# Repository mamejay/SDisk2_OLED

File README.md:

***** Updated Version Using SMD Components *****

I have updated the PCB to use all SMD components and tactile switches
I have re-compiled the code and confirmed is working.

# SDisk2 - Simplified

Disk II flopy drive emulator for Apple 2 computers

Objective. an Open Source Disk II floppy Disk emulator that is easy to make.  
See readme in firmware and PCB section for related info.

## Changes

* 27Mhz Xtal.
* OLED only. All LCD and Nokia LCD codes have been removed.
* All Screen rotation code removed.
* Buttons re-arranged

## To-do

1. Better documentaion of the code.

This project will be migrated to an ESP32 based SDISKII.
<https://github.com/terenceang/sdisk2esp>

## Authors

* (c) 2010 Koichi NISHIDA <tulip-house@msf.biglobe.ne.jp>
* (c) 2012 Victor Trucco
* (c) 2012 Fábio Belavenuto
* (c) 2015 Alexandre Suaide
* (c) 2022 Terence Ang

## License

This work is released under the version 3 of the GNU General Public License.

'''NOTE:'''
The current legal status of this code is uncertain.

Fábio and Alexandre have published files with a header that references the version 3 of the GNU General Public License, but it is not clear yet what's the licensing chosen by the original author, Koichi Nishida.

This repository will be updated once the actual licensing info is clarified by the authors.

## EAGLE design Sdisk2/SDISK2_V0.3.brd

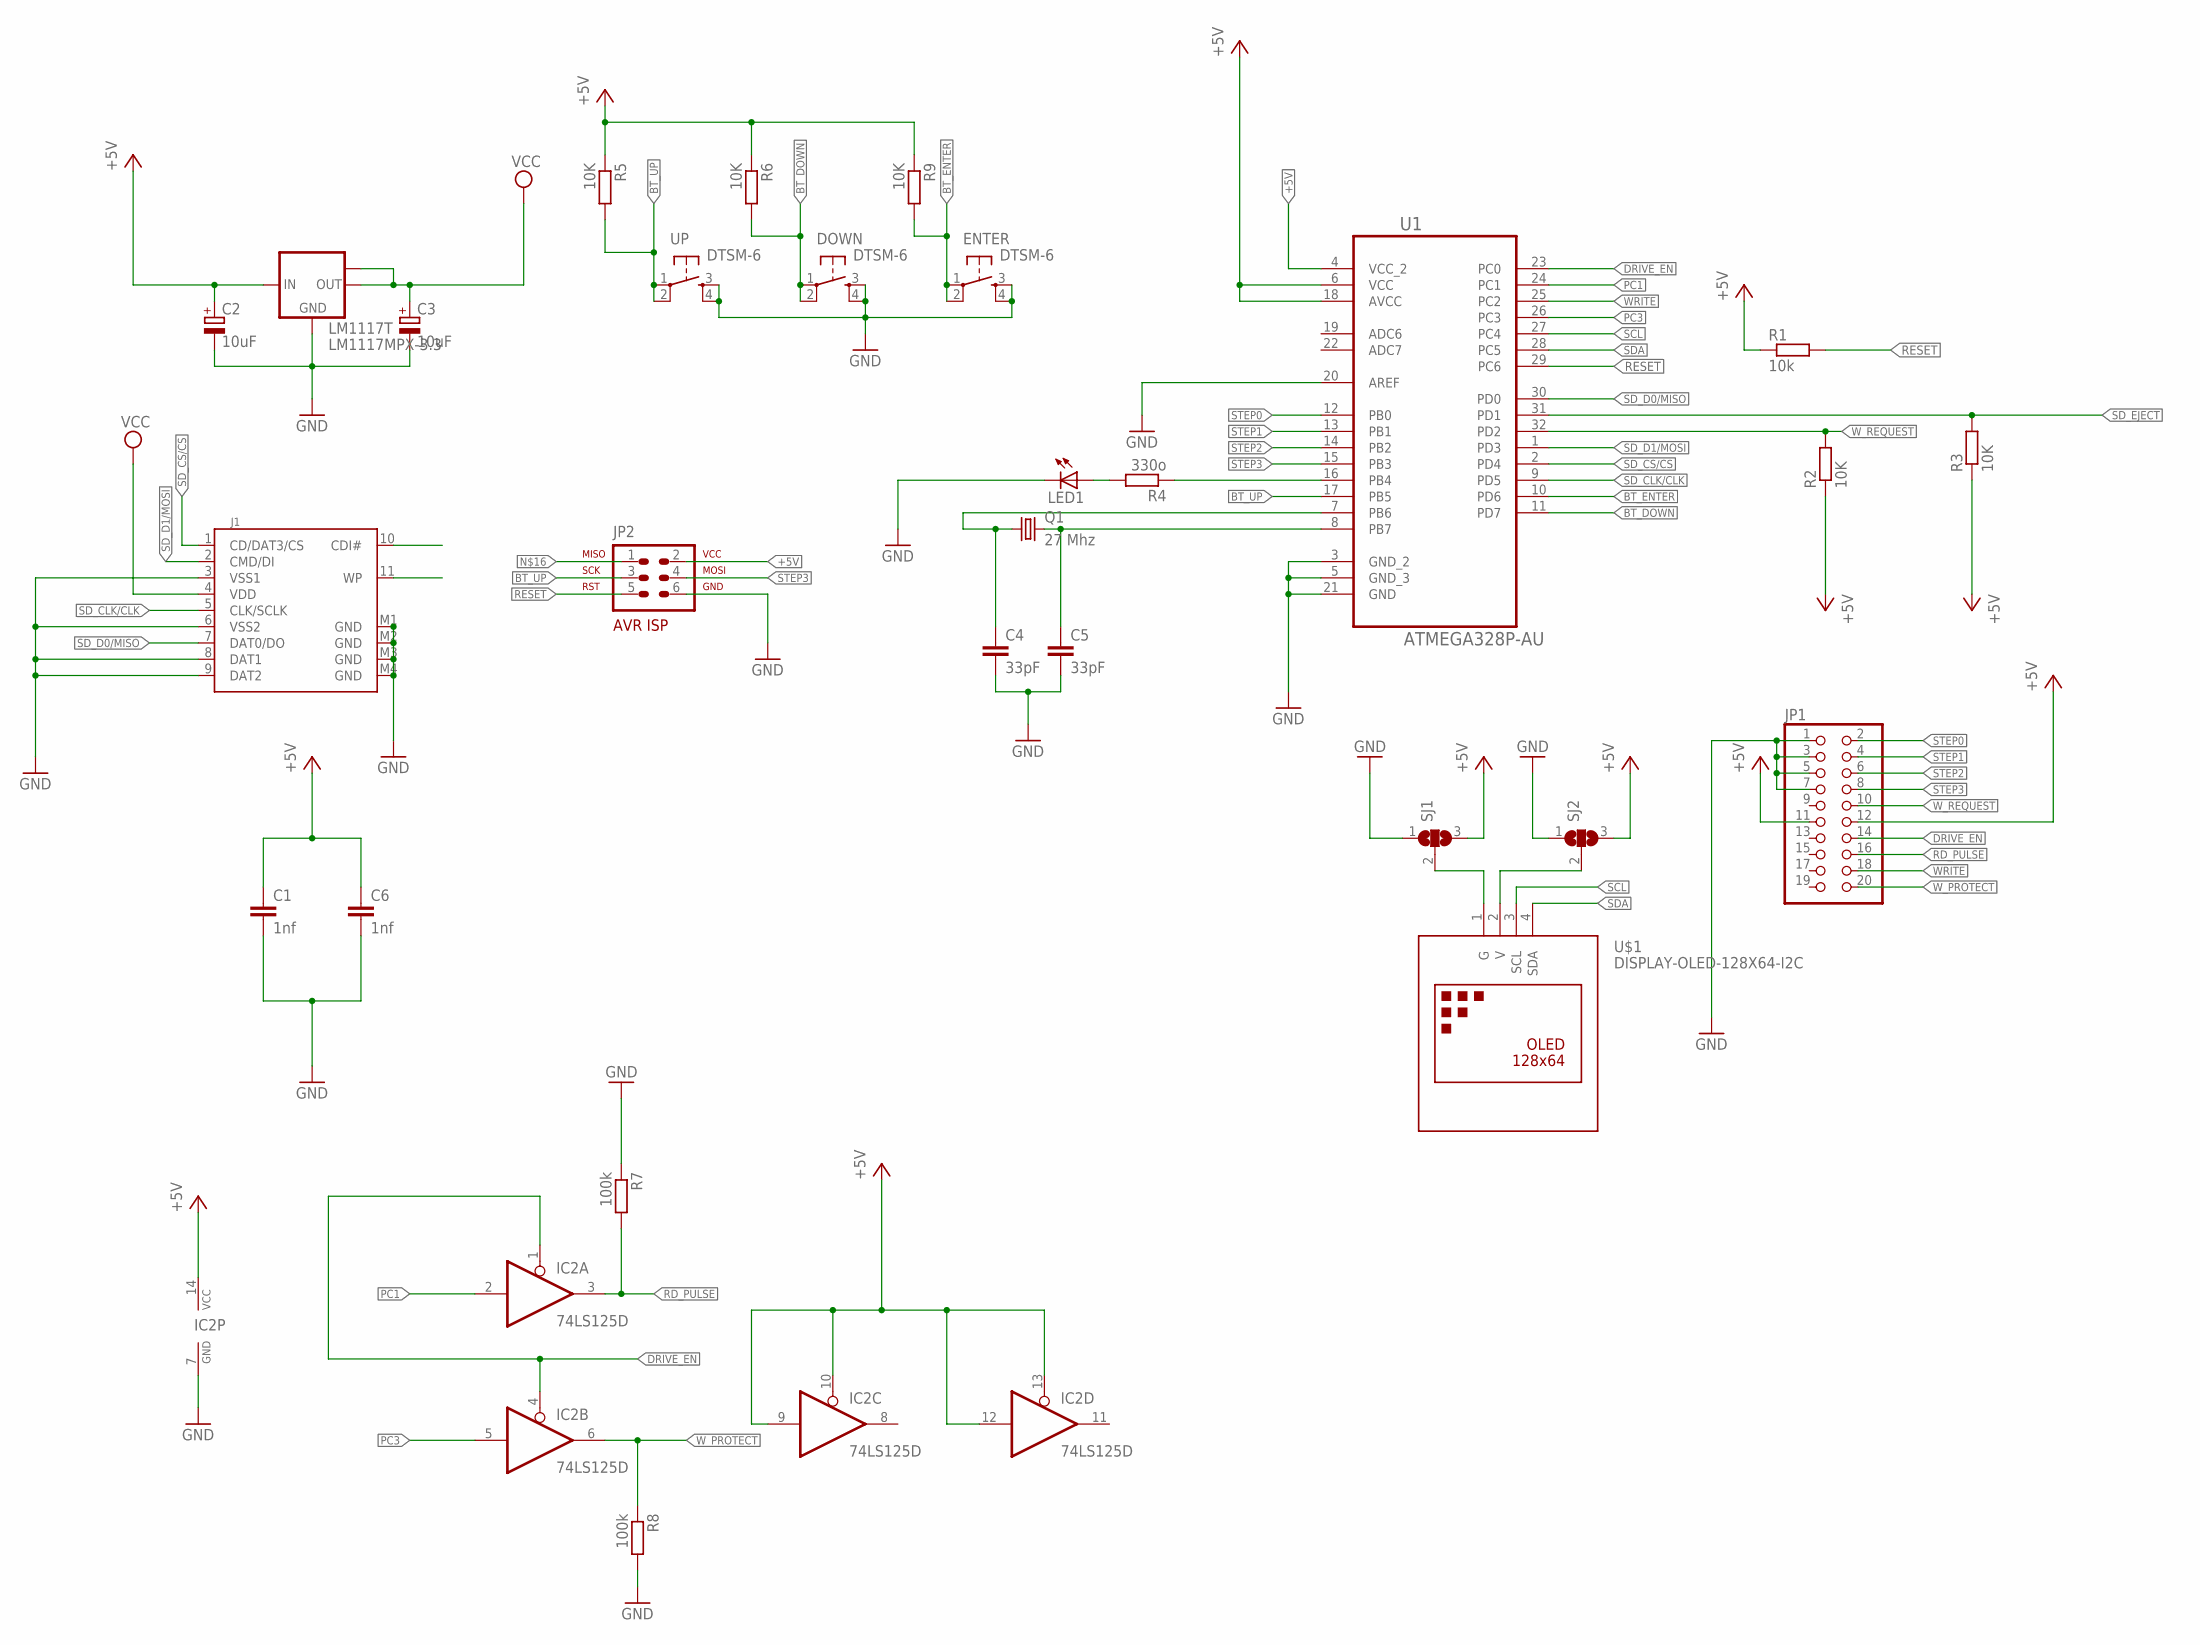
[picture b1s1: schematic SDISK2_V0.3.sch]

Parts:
C1, C6: 1nf; C0805
C2, C3: 10uF; 153CLV-0405
C4, C5: 33pF; C0805
DOWN: DTSM-6
ENTER: DTSM-6
IC2: 74LS125D; SO14
J1: SDCARD; SDCMF-10915W010
JP1: PINHD-2X10_IDC2X10_IDC_NEW; 2X10_IDC
JP2: AVR-ISP-6VERT; AVR-ISP-6
LED1: LEDSML1206; SML1206
LM1117T: LM1117MPX-3.3; SOT223
Q1: 27 Mhz; HC49UP
R1: 10k; R0805
R2, R3, R5, R6, R9: 10K; R0805
R4: 330o; R0805
R7, R8: 100k; R0805
SJ1, SJ2: SJ2W; SJ_2
U1: ATMEGA328P-AU; QFP80P900X900X120-32N
U$1: DISPLAY-OLED-128X64-I2C
UP: DTSM-6

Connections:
3.3V: C3.+, J1.4 (VDD), LM1117T.2 (OUT), LM1117T.TAB (OUT1)
+5V: C1.1, C2.+, C6.1, IC2.9 (I), IC2.10 (OE), IC2.12 (I), IC2.13 (OE), IC2.14 (VCC), JP1.11, JP1.12, JP2.2, LM1117T.3 (IN), R1.1, R2.1, R3.1, R5.1, R6.1, R9.1, SJ1.3, SJ2.3, U1.4 (VCC_2), U1.6 (VCC), U1.18 (AVCC)
BT_DOWN: DOWN.1, DOWN.2, R6.2, U1.11 (PD7)
BT_ENTER: ENTER.1, ENTER.2, R9.2, U1.10 (PD6)
BT_UP: JP2.3, R5.2, U1.17 (PB5), UP.1, UP.2
DRIVE_EN: IC2.1 (OE), IC2.4 (OE), JP1.14, U1.23 (PC0)
GND: C1.2, C2.-, C3.-, C4.2, C5.2, C6.2, DOWN.3, DOWN.4, ENTER.3, ENTER.4, IC2.7 (GND), J1.3 (VSS1), J1.6 (VSS2), J1.8 (DAT1), J1.9 (DAT2), J1.M1 (GND), J1.M2 (GND), J1.M3 (GND), J1.M4 (GND), JP1.1, JP1.3, JP1.5, JP1.7, JP2.6, LED1.C, LM1117T.1 (GND), R7.1, R8.2, SJ1.1, SJ2.1, U1.3 (GND_2), U1.5 (GND_3), U1.20 (AREF), U1.21 (GND), UP.3, UP.4
unnamed: C4.1, Q1.1, U1.7 (PB6)
unnamed: LED1.A, R4.2
unnamed: SJ1.2, U$1.1 (G)
unnamed: SJ2.2, U$1.2 (V)
unnamed: JP2.1, R4.1, U1.16 (PB4)
unnamed: C5.1, Q1.2, U1.8 (PB7)
PC1: IC2.2 (I), U1.24 (PC1)
PC3: IC2.5 (I), U1.26 (PC3)
RD_PULSE: IC2.3 (O), JP1.16, R7.2
RESET: JP2.5, R1.2, U1.29 (PC6)
SCL: U1.27 (PC4), U$1.3 (SCL)
SDA: U1.28 (PC5), U$1.4 (SDA)
SD_CLK/CLK: J1.5 (CLK/SCLK), U1.9 (PD5)
SD_CS/CS: J1.1 (CD/DAT3/CS), U1.2 (PD4)
SD_D0/MISO: J1.7 (DAT0/DO), U1.30 (PD0)
SD_D1/MOSI: J1.2 (CMD/DI), U1.1 (PD3)
SD_EJECT: R3.2, U1.31 (PD1)
STEP0: JP1.2, U1.12 (PB0)
STEP1: JP1.4, U1.13 (PB1)
STEP2: JP1.6, U1.14 (PB2)
STEP3: JP1.8, JP2.4, U1.15 (PB3)
WRITE: JP1.18, U1.25 (PC2)
W_PROTECT: IC2.6 (O), JP1.20, R8.1
W_REQUEST: JP1.10, R2.2, U1.32 (PD2)

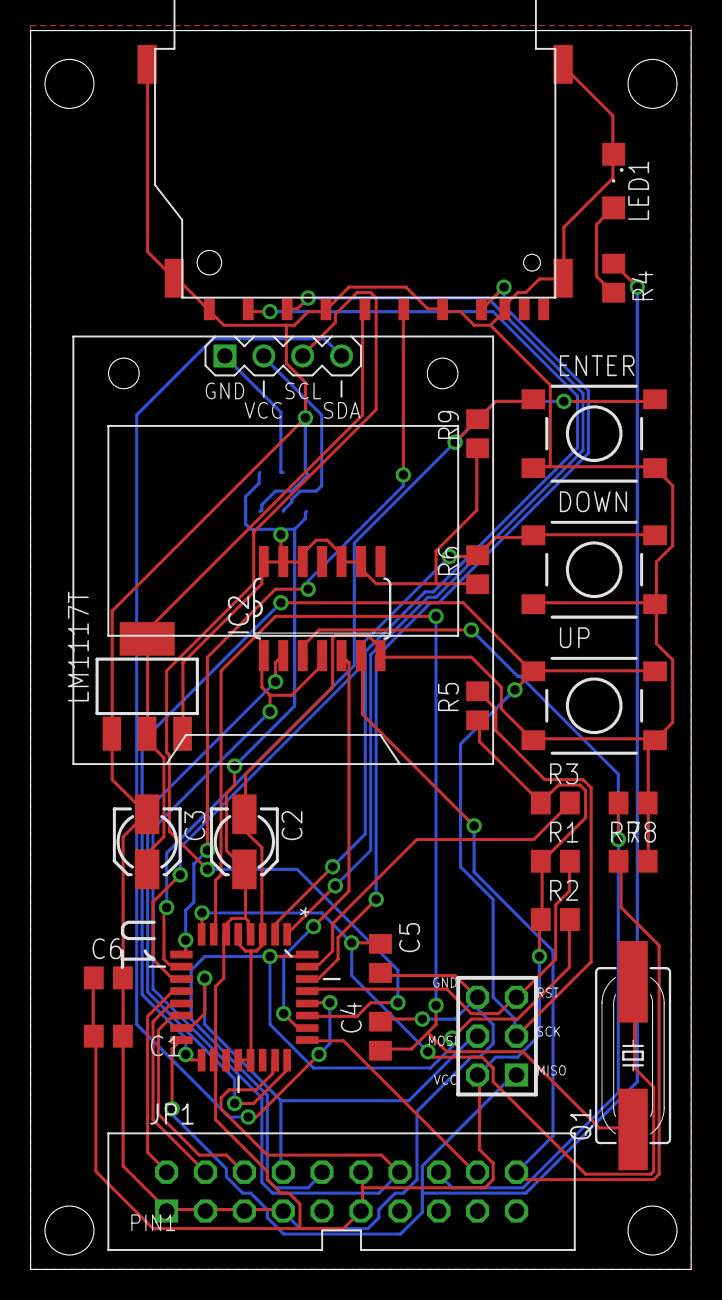
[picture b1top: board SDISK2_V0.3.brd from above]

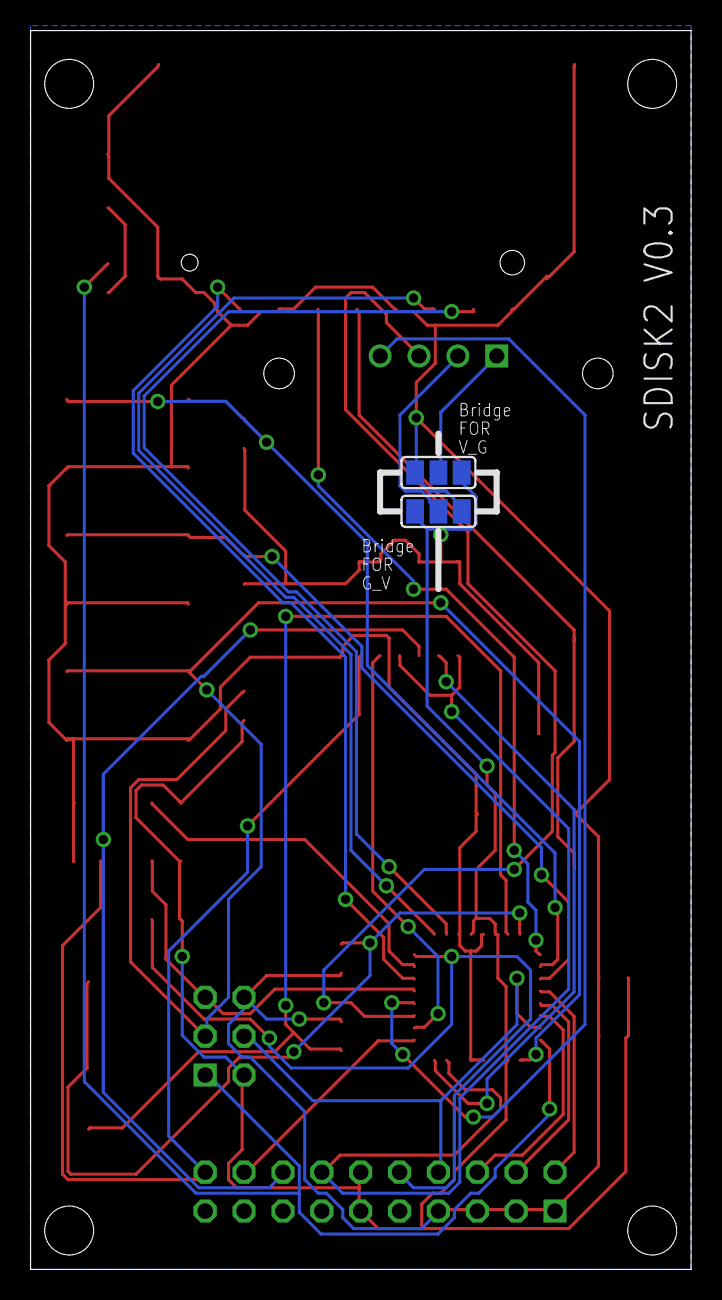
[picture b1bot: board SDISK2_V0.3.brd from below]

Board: 2 copper layers, 43.2 x 81.0 mm, 29 parts (2 on the bottom side), 31 nets.

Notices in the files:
parts and their libraries:
diy-modulesCUSTOM: Released under the Creative Commons Attribution 4.0 International License: http://creativecommons.org/licenses/by/4.0
